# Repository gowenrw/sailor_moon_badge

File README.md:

# sailor_moon_badge

Sailor Moon Badge Artifacts

This is a DEFCON Indie badge created for DC31.

This is where all the files for the Badge will be stored.

This includes code and art and cad and fab files.  All the things.

## File Structure

This is the file structure of this repository

* [/](/README.md) - YOU ARE HERE
* [/art/](./art/) - Artwork and other graphics created by this project
  * [/art/inspiration/](./art/inspiration/) - Art and graphics pulled from other sources used as inspiration for this project
  * [/art/fonts/](./art/fonts/) - Fonts used in art and graphics
* [/code/](./code/) - All project related Code / Firmware
* [/docs/](./docs/) - Documentation created by this project including web pages
* [/eda/](./eda/) - Electronic Design Automation files (i.e. KiCad)
  * [/eda/sailor_moon/](./eda/sailor_moon/) - KiCad 6.x project folder for the future_badge PCB
* [/README.md](/README.md) - This File
* [/LICENSE](/LICENSE) - Currently set to MIT

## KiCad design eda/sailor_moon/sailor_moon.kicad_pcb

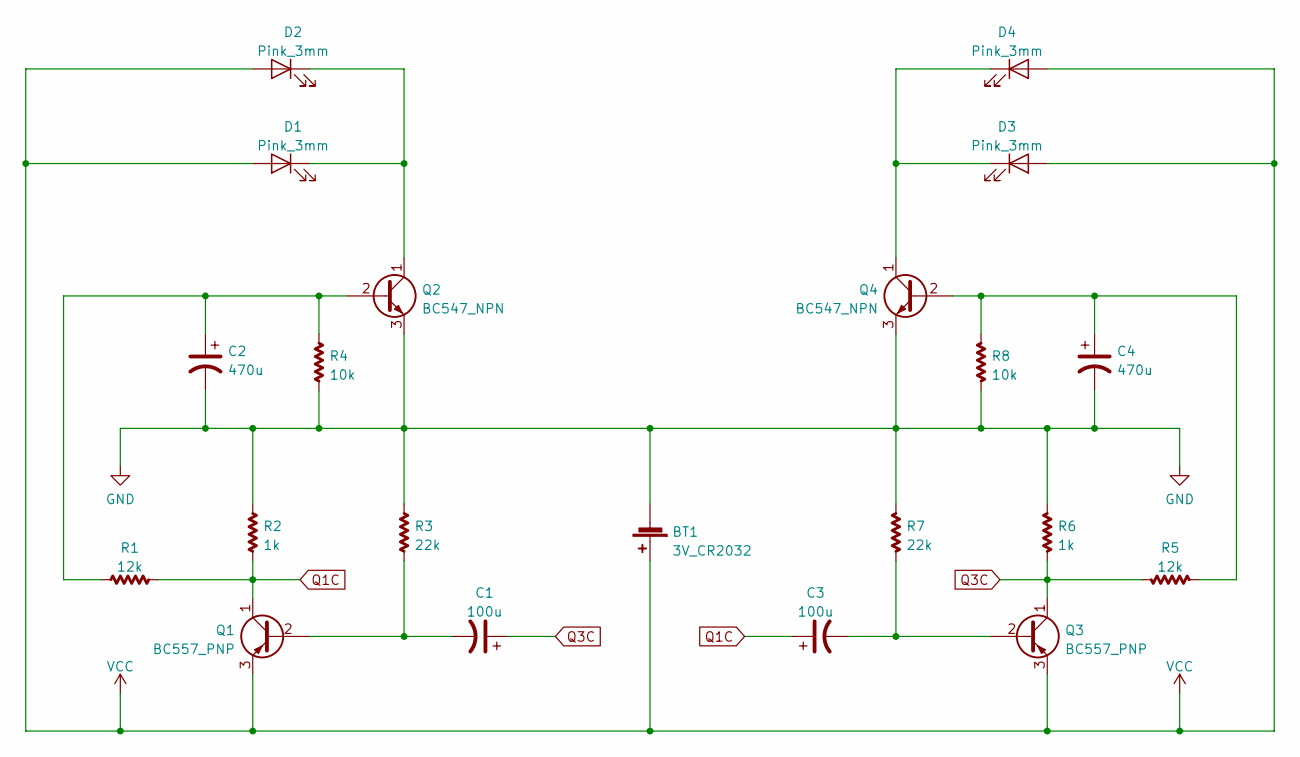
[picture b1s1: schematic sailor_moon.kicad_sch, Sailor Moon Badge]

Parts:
BT1: 3V_CR2032; BatteryHolder_CR2032-BS-2-1_Back_backsilk
C1, C3: 100u; CP_Radial_D6.3mm_P2.50mm_back
C2, C4: 470u; CP_Radial_D6.3mm_P2.50mm_back
D1, D2, D3, D4: Pink_3mm; LED_D3.0mm-2_back
Q1, Q3: BC557_PNP; Q_BC557_TO-92_back
Q2, Q4: BC547_NPN; Q_BC547_TO-92_back
R1, R5: 12k; R_Axial_DIN0207_L6.3mm_D2.5mm_P7.62mm_Horizontal_back
R2, R6: 1k; R_Axial_DIN0207_L6.3mm_D2.5mm_P7.62mm_Horizontal_back
R3, R7: 22k; R_Axial_DIN0207_L6.3mm_D2.5mm_P7.62mm_Horizontal_back
R4, R8: 10k; R_Axial_DIN0207_L6.3mm_D2.5mm_P7.62mm_Horizontal_back

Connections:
GND: BT1.2 (-), C2.2, C4.2, Q2.3 (E), Q4.3 (E), R2.1, R3.1, R4.2, R6.1, R7.1, R8.2
unnamed: C1.2, Q1.2 (B), R3.2
unnamed: C2.1, Q2.2 (B), R1.1, R4.1
unnamed: C3.2, Q3.2 (B), R7.2
unnamed: C4.1, Q4.2 (B), R5.1, R8.1
unnamed: D1.1 (K), D2.1 (K), Q2.1 (C)
unnamed: D3.1 (K), D4.1 (K), Q4.1 (C)
Q1C: C3.1, Q1.1 (C), R1.2, R2.2
Q3C: C1.1, Q3.1 (C), R5.2, R6.2
VCC: BT1.1 (+), D1.2 (A), D2.2 (A), D3.2 (A), D4.2 (A), Q1.3 (E), Q3.3 (E)

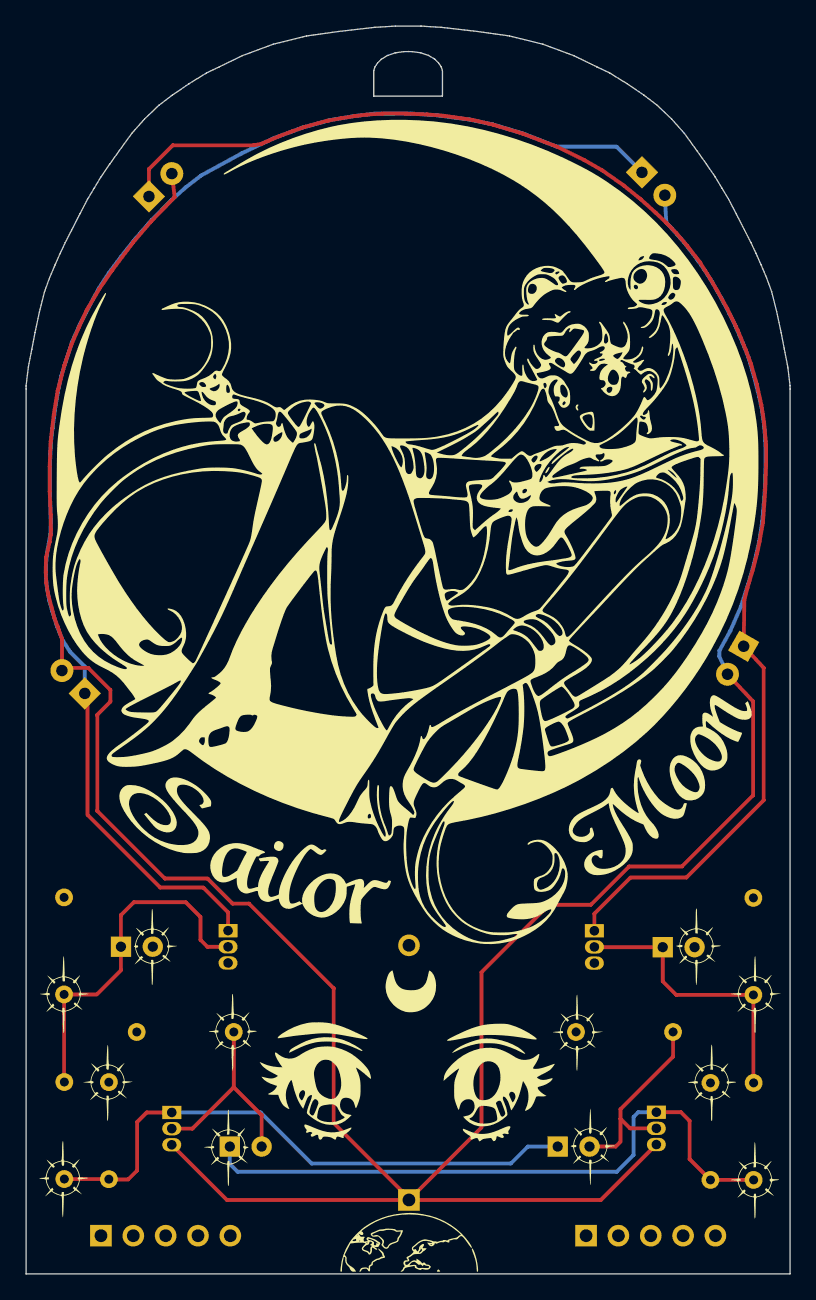
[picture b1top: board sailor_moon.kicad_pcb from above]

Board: 2 copper layers, 60.0 x 98.0 mm, 25 parts (0 on the bottom side), 10 nets.

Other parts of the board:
Bot_Silk_Front: LOGO; 0_sailor_moon_bot_silkf_w60mm
Mask_Back: LOGO; 0_sailor_moon_maskb_w60mm
Mask_Front: LOGO; 0_sailor_moon_maskf_w60mm
Silk_Front: LOGO; 0_sailor_moon_silkf_w60mm

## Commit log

2023-08-03 initial push
2023-08-03 web update
